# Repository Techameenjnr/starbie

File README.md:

# Starbie 🐾

A tiny motion-controlled digital pet built around the Seeed Studio XIAO ESP32-C3. Starbie uses a small OLED face, two buttons, an MPU6050 motion sensor, and an optional DHT11 environment sensor.

## What it does

- Displays a little animated pet on a 128×64 OLED.
- Uses the MPU6050 to steer a four-choice menu by tilting the board.
- Uses two buttons to open/select the menu and show or hide stats.
- Includes NAP, PLAY, FEED, and PET actions.
- Saves the pet's joy, energy, and fullness between restarts.
- Reads temperature and humidity when a DHT11 is fitted.

## Hardware

- Seeed Studio XIAO ESP32-C3
- 0.96-inch I²C OLED (SSD1306, 128×64)
- MPU6050 module
- Two momentary push buttons
- DHT11 sensor (optional)
- Custom PCB and connecting headers

## Pin mapping

| Function | XIAO pin | ESP32-C3 GPIO |
|---|---|---:|
| OLED + MPU6050 SDA | D5 | 7 |
| OLED + MPU6050 SCL | D4 | 6 |
| DHT11 data | D1 | 3 |
| Button 1 | D2 | 4 |
| Button 2 | D3 | 5 |

The OLED and MPU6050 share the I²C bus. Confirm module pin order and the final schematic before powering hardware.

## Firmware

The Arduino sketch is in [Firmware/Starbie/Starbie.ino](Firmware/Starbie/Starbie.ino).

Install the ESP32 board package and these Arduino libraries:
- Adafruit GFX Library
- Adafruit SSD1306
- Adafruit MPU6050
- DHT sensor library

Select **XIAO_ESP32C3** as the board in Arduino IDE.

## PCB design status

The KiCad schematic and PCB source files are included in this repository:

- [PCB layout](starbie.kicad_pcb)
- [Schematic](starbie.kicad_sch)
- [KiCad project settings](starbie.kicad_pro)

The board is routed. The latest KiCad DRC reports zero unconnected items and zero schematic parity issues, with one U1 local footprint library mismatch warning. The board is not confirmed fabrication-ready, so manufacturing outputs are not included.

## CAD enclosure

The Week 2 parametric Starbie Shell model is in [cad/starbie_shell.scad](cad/starbie_shell.scad), with assumptions and verification notes in [cad/README.md](cad/README.md). The final OpenSCAD exports are [cad/exports/starbie_shell_base.stl](cad/exports/starbie_shell_base.stl) (73.5 × 64 × 18 mm) and [cad/exports/starbie_shell_lid.stl](cad/exports/starbie_shell_lid.stl) (77.8 × 68.3 × 8 mm). OpenSCAD export and mesh inspection found each STL to be one connected, closed mesh. These checks do not verify component clearance, physical fit, strength, or printability; connector and control openings also remain unverified.

### PCB photo

A genuine KiCad PCB Editor screenshot should be added here after capturing the board in PCB Editor. No PCB screenshot is included yet.

## Project log

See [JOURNAL.md](JOURNAL.md) for the project planning entry and [BOM.md](BOM.md) for the parts-funding record.

## Credits

Starbie is based on the Week 1 guide and starter firmware from [SharKingStudios/Starbie](https://github.com/SharKingStudios/Starbie). This repository records my own build progress and future hardware changes.
## PCB Design

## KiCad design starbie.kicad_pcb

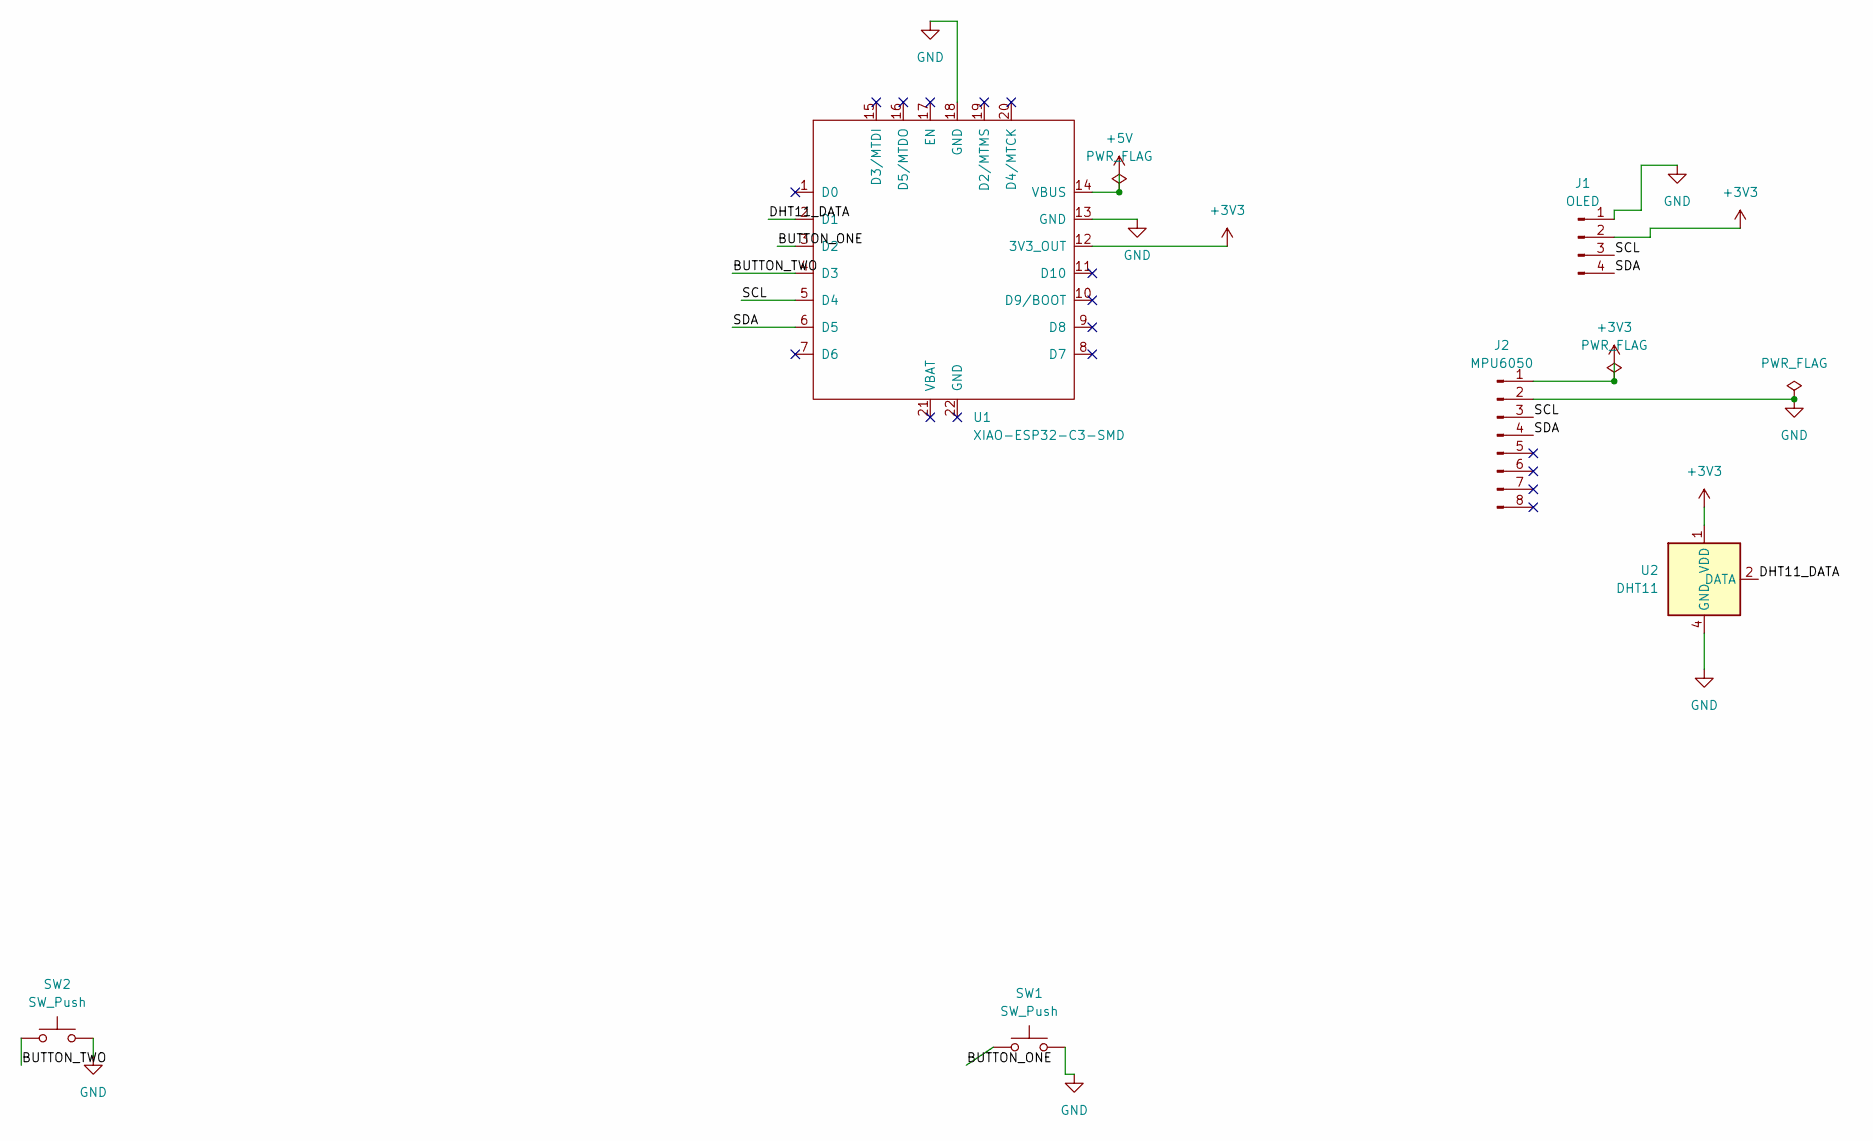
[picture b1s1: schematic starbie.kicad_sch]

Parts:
J1: OLED; PinSocket_1x04_P2.54mm_Horizontal
J2: MPU6050; PinSocket_1x08_P2.54mm_Horizontal
SW1, SW2: SW_Push; SW_PUSH_6mm
U1: XIAO-ESP32-C3-SMD
U2: DHT11; Aosong_DHT11_5.5x12.0_P2.54mm

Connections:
+3V3: J1.2, J2.1, U1.12 (3V3_OUT), U2.1 (VDD)
+5V: U1.14 (VBUS)
/BUTTON_ONE: SW1.1, U1.3 (D2)
/BUTTON_TWO: SW2.1, U1.4 (D3)
/DHT11_DATA: U1.2 (D1), U2.2 (DATA)
/SCL: J1.3, J2.3, U1.5 (D4)
/SDA: J1.4, J2.4, U1.6 (D5)
GND: J1.1, J2.2, SW1.2, SW2.2, U1.13 (GND), U1.18 (GND), U2.4 (GND)

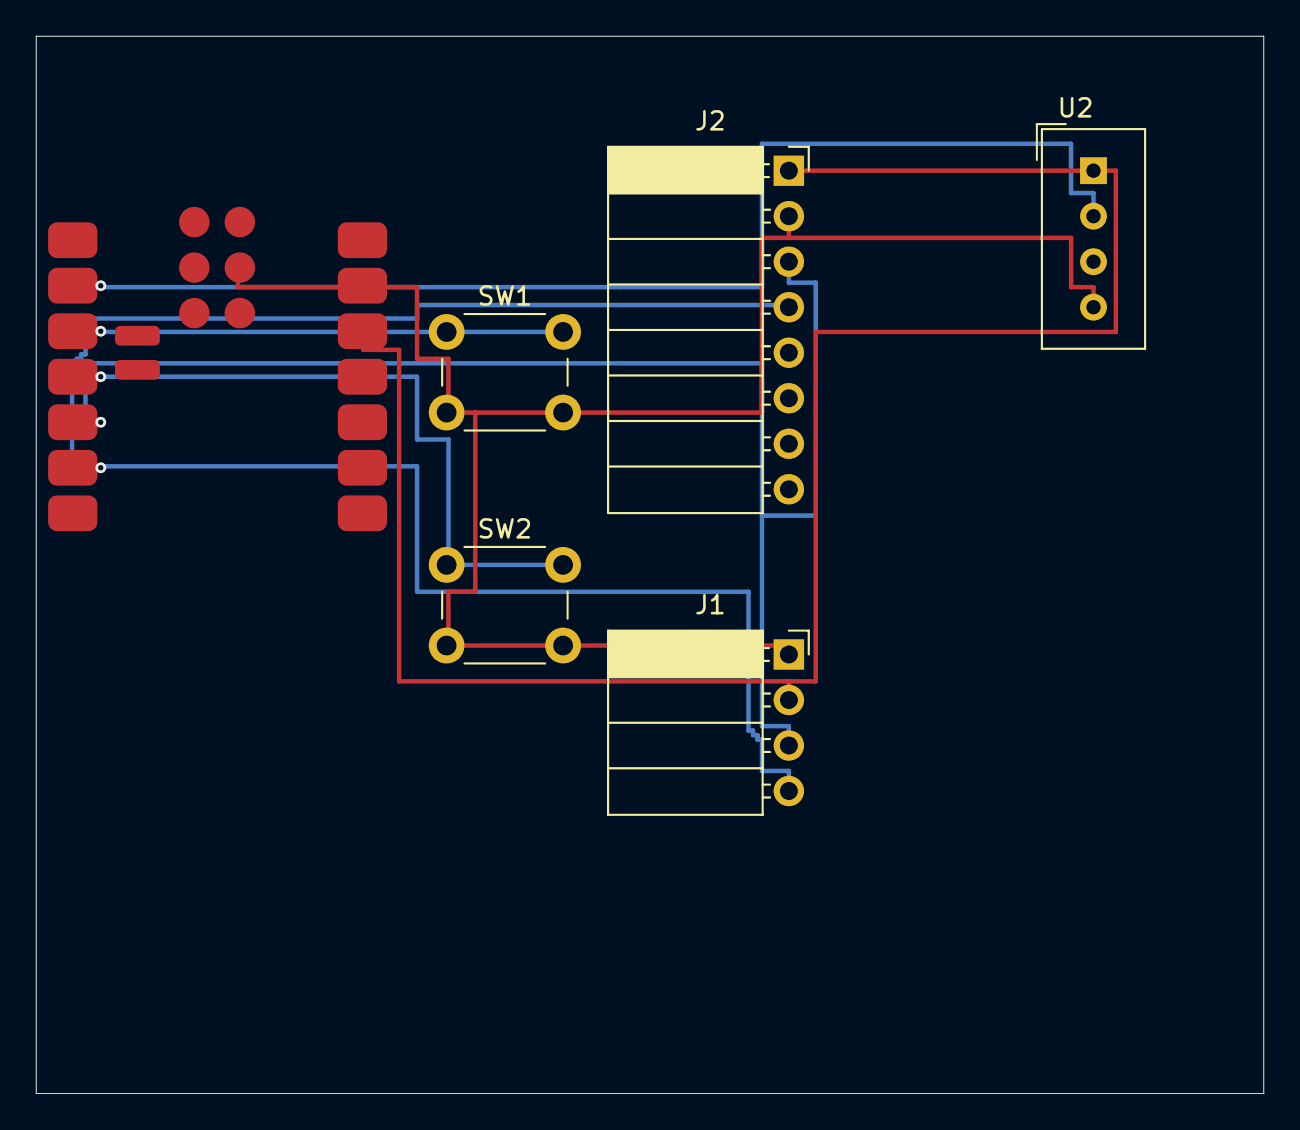
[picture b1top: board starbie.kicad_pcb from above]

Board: 2 copper layers, 68.5 x 59.0 mm, 6 parts (0 on the bottom side), 7 nets.

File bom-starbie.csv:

Reference,Quantity,Value,Notes
J1,1,Connector,Confirm exact connector specification
J2,1,Connector,Confirm exact connector specification
SW1,1,Switch,Confirm exact switch specification
SW2,1,Switch,Confirm exact switch specification
U1,1,XIAO-ESP32-C3-SMD,Microcontroller module
U2,1,DHT11,Temperature and humidity sensor
